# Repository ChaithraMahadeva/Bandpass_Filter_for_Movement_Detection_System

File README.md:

# Bandpass_Filter_for_Movement_Detection_System
Design and Implementation of a Bandpass Filter and an active Amplifier for 24GHz Radar Movement Detection System. The schematic and layout has been designed in KiCAD PCB Design Tool and simulated in LTspice. The hardware has been integrated with PSoC 5LP Development board and tested for the results.

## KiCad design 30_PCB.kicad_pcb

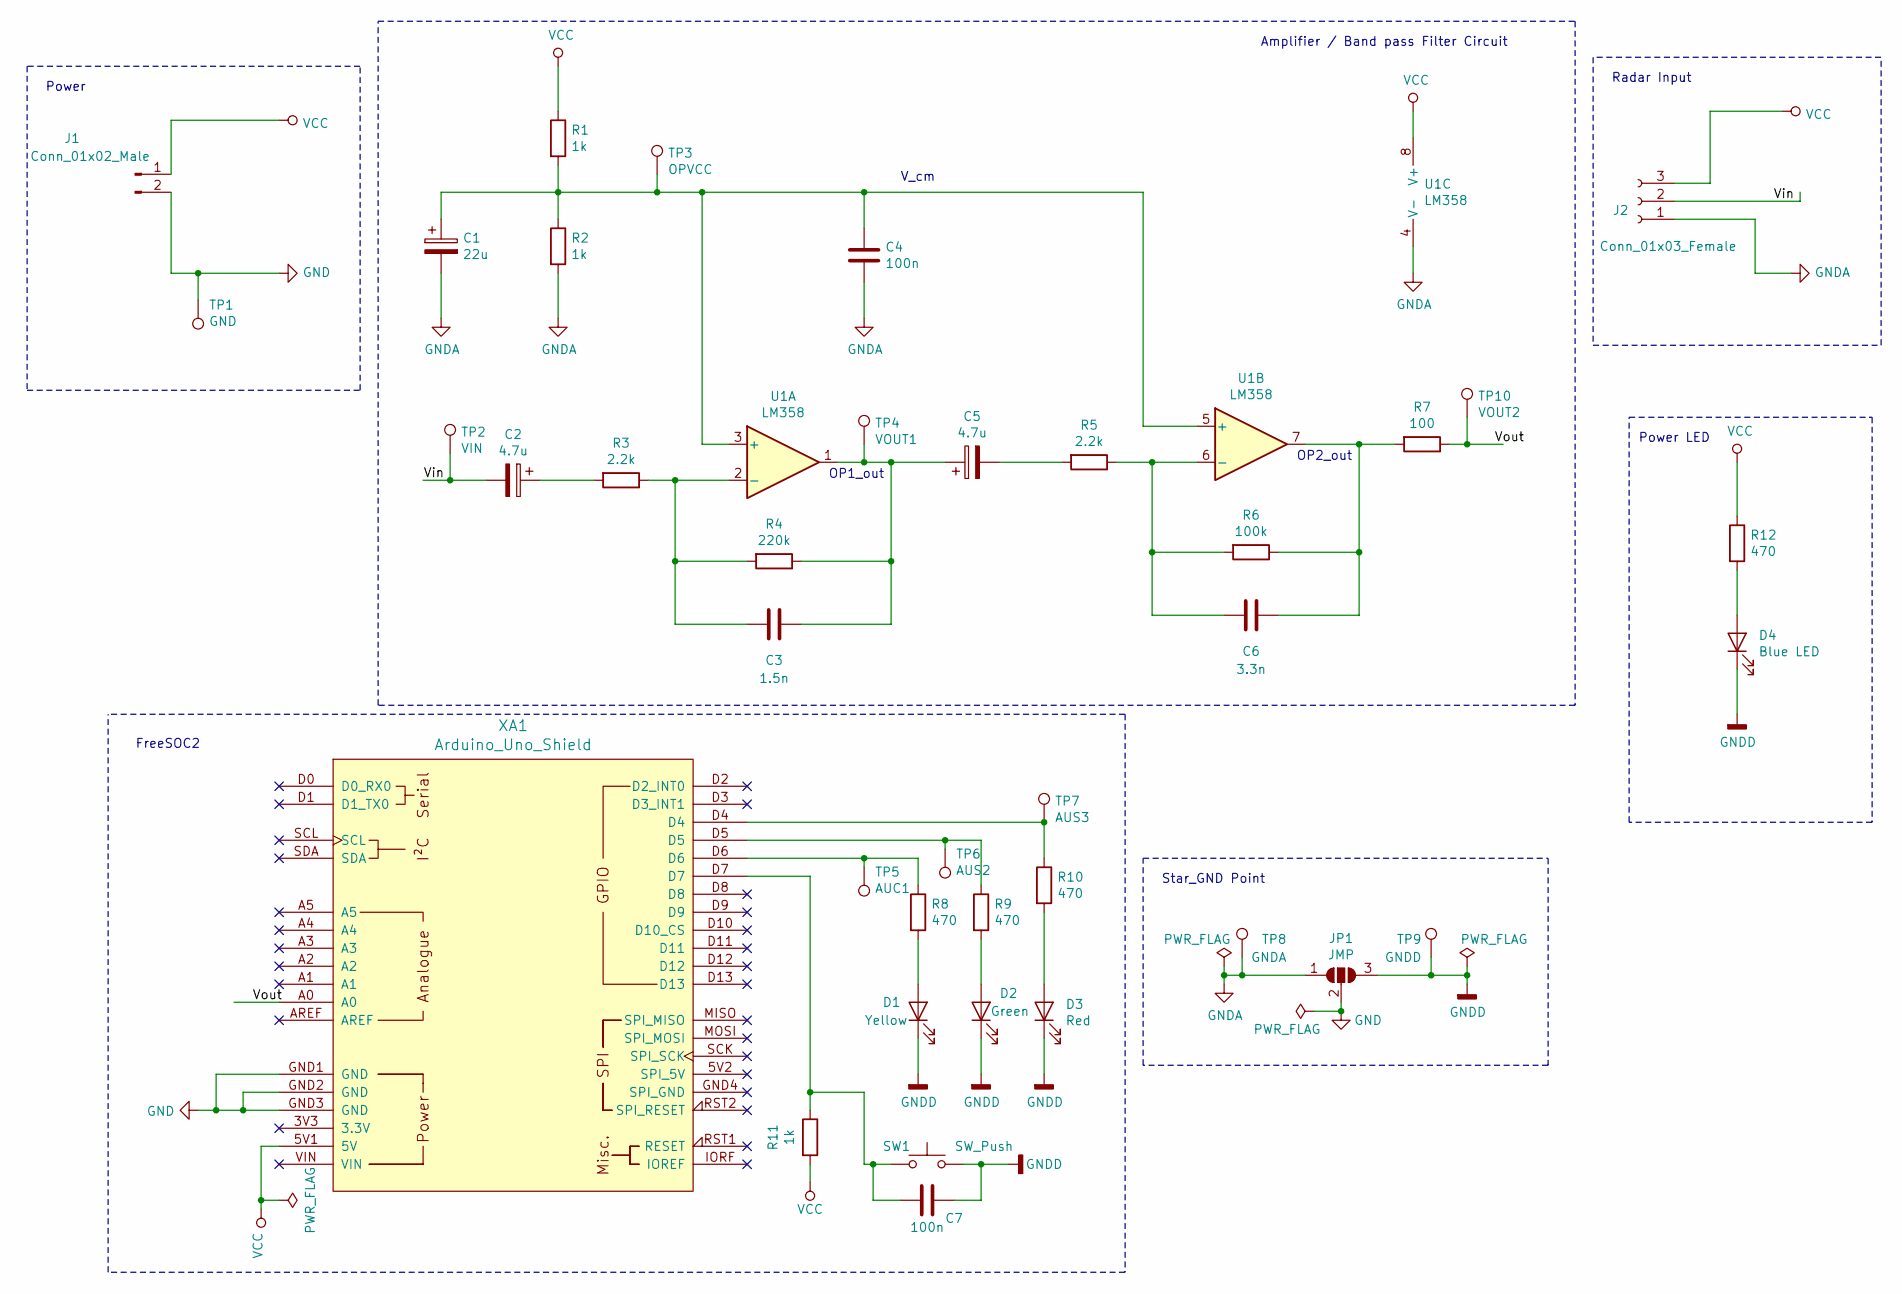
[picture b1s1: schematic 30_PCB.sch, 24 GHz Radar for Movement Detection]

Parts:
C1: 22u; CP_Radial_D5.0mm_P2.00mm
C2, C5: 4.7u; CP_Radial_D5.0mm_P2.00mm
C3: 1.5n; C_Rect_L7.2mm_W4.5mm_P5.00mm_FKS2_FKP2_MKS2_MKP2
C4: 100n; C_Rect_L7.2mm_W2.5mm_P5.00mm_FKS2_FKP2_MKS2_MKP2
C6: 3.3n; C_Rect_L7.2mm_W4.5mm_P5.00mm_FKS2_FKP2_MKS2_MKP2
C7: 100n; C_1206_3216Metric_Pad1.42x1.75mm_HandSolder
D1: Yellow; LED_1206_3216Metric_Pad1.42x1.75mm_HandSolder
D2: Green; LED_1206_3216Metric_Pad1.42x1.75mm_HandSolder
D3: Red; LED_1206_3216Metric_Pad1.42x1.75mm_HandSolder
D4: Blue LED; LED_1206_3216Metric_Pad1.42x1.75mm_HandSolder
J1: Conn_01x02_Male; PinHeader_1x02_P2.54mm_Vertical
J2: Conn_01x03_Female; PinSocket_1x03_P2.54mm_Horizontal
JP1: JMP; SolderJumper-3_P1.3mm_Open_RoundedPad1.0x1.5mm
R1, R2: 1k; R_Axial_DIN0204_L3.6mm_D1.6mm_P7.62mm_Horizontal
R3, R5: 2.2k; R_Axial_DIN0204_L3.6mm_D1.6mm_P7.62mm_Horizontal
R4: 220k; R_Axial_DIN0204_L3.6mm_D1.6mm_P7.62mm_Horizontal
R6: 100k; R_Axial_DIN0204_L3.6mm_D1.6mm_P7.62mm_Horizontal
R7: 100; R_Axial_DIN0204_L3.6mm_D1.6mm_P7.62mm_Horizontal
R8, R9, R10, R12: 470; R_1206_3216Metric_Pad1.42x1.75mm_HandSolder
R11: 1k; R_1206_3216Metric_Pad1.42x1.75mm_HandSolder
SW1: SW_Push; SW_PUSH_6mm_H4.3mm
TP1: GND; TestPoint_Plated_Hole_D2.0mm
TP2: VIN; TestPoint_Plated_Hole_D2.0mm
TP3: OPVCC; TestPoint_Plated_Hole_D2.0mm
TP4: VOUT1; TestPoint_Plated_Hole_D2.0mm
TP5: AUC1; TestPoint_Plated_Hole_D2.0mm
TP6: AUS2; TestPoint_Plated_Hole_D2.0mm
TP7: AUS3; TestPoint_Plated_Hole_D2.0mm
TP8: GNDA; TestPoint_Plated_Hole_D2.0mm
TP9: GNDD; TestPoint_Plated_Hole_D2.0mm
TP10: VOUT2; TestPoint_Plated_Hole_D2.0mm
U1: LM358; DIP-8_W7.62mm_Socket
XA1: Arduino_Uno_Shield

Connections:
/Vin: C2.2, J2.2, TP2.1
/Vout: R7.1, TP10.1, XA1.A0
GND: J1.2, JP1.2 (C), TP1.1, XA1.GND1 (GND), XA1.GND2 (GND), XA1.GND3 (GND)
GNDA: C1.2, C4.2, J2.1, JP1.1 (A), R2.2, TP8.1, U1.4 (V-)
GNDD: C7.1, D1.1 (K), D2.1 (K), D3.1 (K), D4.1 (K), JP1.3 (B), SW1.2, TP9.1
unnamed: C1.1, C4.1, R1.2, R2.1, TP3.1, U1.3 (+), U1.5 (+)
unnamed: C2.1, R3.2
unnamed: C3.1, R3.1, R4.2, U1.2 (-)
unnamed: C3.2, C5.1, R4.1, TP4.1, U1.1
unnamed: C5.2, R5.2
unnamed: C6.1, R6.1, R7.2, U1.7
unnamed: C6.2, R5.1, R6.2, U1.6 (-)
unnamed: C7.2, R11.1, SW1.1, XA1.D7
unnamed: D1.2 (A), R8.2
unnamed: D2.2 (A), R9.2
unnamed: D3.2 (A), R10.2
unnamed: D4.2 (A), R12.2
unnamed: R8.1, TP5.1, XA1.D6
unnamed: R9.1, TP6.1, XA1.D5
unnamed: R10.1, TP7.1, XA1.D4
VCC: J1.1, J2.3, R1.1, R11.2, R12.1, U1.8 (V+), XA1.5V1 (5V)

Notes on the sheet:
V_cm
OP1_out
OP2_out
FreeSOC2
Amplifier / Band pass Filter Circuit
Radar Input
Power
Power LED
Star_GND Point

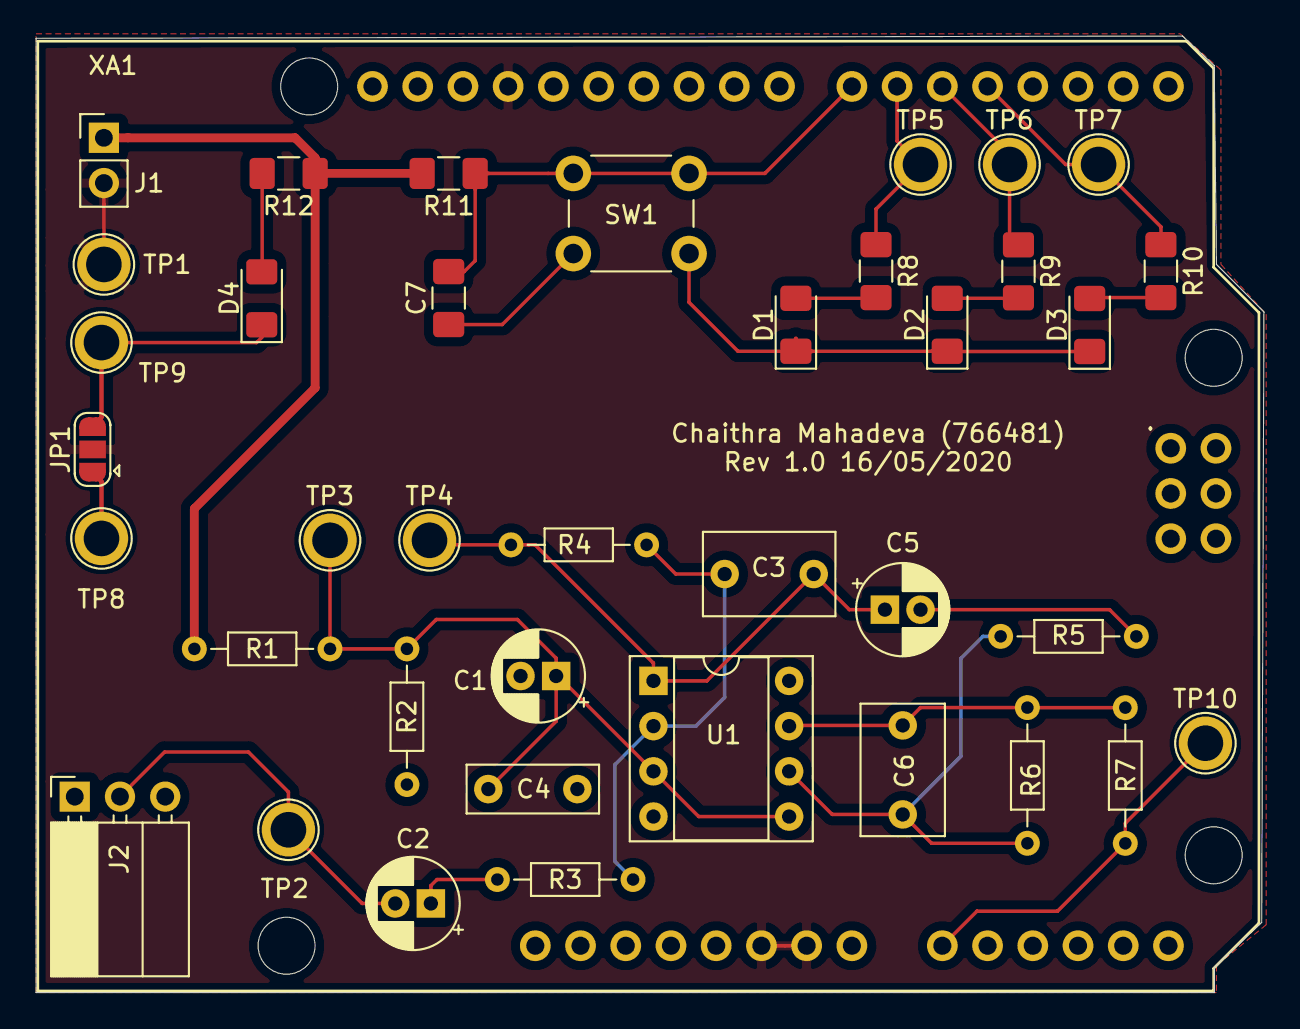
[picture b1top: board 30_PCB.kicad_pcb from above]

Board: 4 copper layers, 69.0 x 53.7 mm, 39 parts (0 on the bottom side), 21 nets.
